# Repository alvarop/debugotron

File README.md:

# Debugotron!

Debugotron is a collection of debugging/automation tools I've wanted in the past but didn't have access to. Currently, the tools include:

## SWD to USB-C!

Have you ever wanted to debug your device over USB-C? Sometimes there's not enough room for a JTAG/SWD connector, or even TAGConnect pads! The USB-C specification has a Debug Accessory Mode feature that allows for this. I have a [Twitter thread](https://twitter.com/alvaroprieto/status/1495860045728395278) with additional details. [Here's an unrolled version for easier reading.](https://threadreaderapp.com/thread/1495860045728395278.html)

### SWD to USB-C Programmer
Since the current adapter uses an ATTiny24a, I made a different programmer adapter for it

### Example Target
This is a simple STM32L4 board that implements USB-C DAM (the "proper way") as an example.

## SWD Switch
Tool that allows connecting/disconnecting the SWD/JTAG lines (Via ARM 10-pin connector) with a pushbutton (or external signal). This can be useful when trying to measure ultra low power consumption on a device while the debugger is connected (but not necessarily running/attached).

## USB-C Switch
This one is more of an automation tool. I've always wanted to automate firmware testing. Sometimes, having USB connected is necessary to program/communicate with a device, but at the same time, having USB connected changes the power characteristics of the test (or just operating mode).

For example, you might want to automatically test the power consumption of a battery powered device every night with the latest firmware. In order to run the test, you might have to connect to the device, flash it, then disconnect USB. The USB-C switch will allow software-controlled power and data connect/disconnects to a USB-C device. Depending on the configuration, it will also allow full 20V@5A pass-through by allowing USB-PD communication over the CC lines.

In the cases where you want to communicate with a device over USB while still powering it via 20V (or anything higher than 5V), a USB switch allows for a different USB cable to be used for data only, while power is taken from a separate USB-C port.

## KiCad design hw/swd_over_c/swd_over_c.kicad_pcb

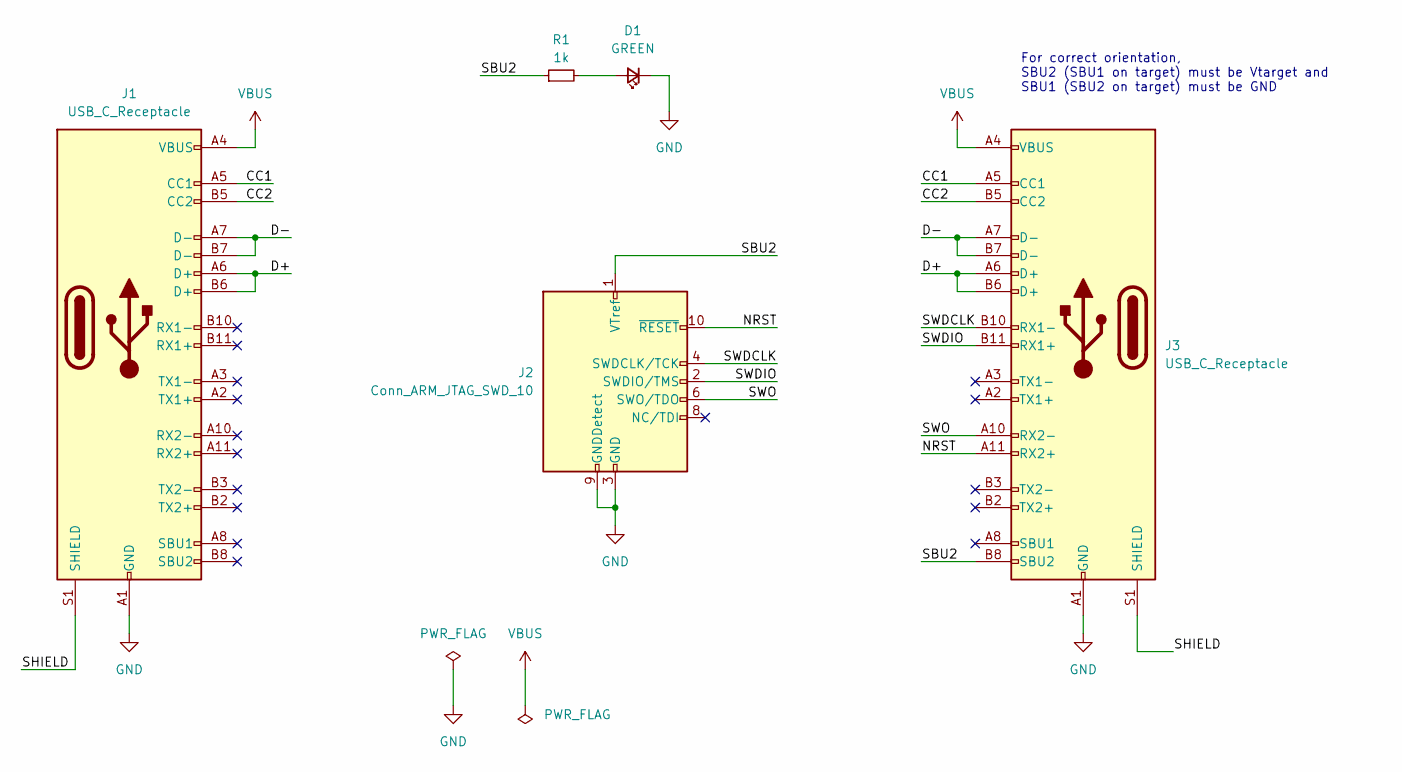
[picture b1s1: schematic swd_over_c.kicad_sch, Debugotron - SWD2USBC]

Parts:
D1: GREEN; LED_0603_1608Metric; MPN SML-D12M8WT86
J1, J3: USB_C_Receptacle; MOLEX-1054500101
J2: Conn_ARM_JTAG_SWD_10; SAMTEC_FTSH-105-01-F-DV-P-TR; MPN FTSH-105-01-F-DV-K
R1: 1k; R_0402_1005Metric; MPN RC0402FR-071KL

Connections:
/CC1: J1.A5 (CC1), J3.A5 (CC1)
/CC2: J1.B5 (CC2), J3.B5 (CC2)
/D+: J1.A6 (D+), J1.B6 (D+), J3.A6 (D+), J3.B6 (D+)
/D-: J1.A7 (D-), J1.B7 (D-), J3.A7 (D-), J3.B7 (D-)
/NRST: J2.10 (~RESET), J3.A11 (RX2+)
/SBU2: J2.1 (VTref), J3.B8 (SBU2), R1.1
/SHIELD: J1.S1 (SHIELD), J3.S1 (SHIELD)
/SWDCLK: J2.4 (SWDCLK/TCK), J3.B10 (RX1-)
/SWDIO: J2.2 (SWDIO/TMS), J3.B11 (RX1+)
/SWO: J2.6 (SWO/TDO), J3.A10 (RX2-)
GND: D1.1 (K), J1.A1 (GND), J1.A12 (GND), J1.B1 (GND), J1.B12 (GND), J2.3 (GND), J2.5 (GND), J2.9 (GNDDetect), J3.A1 (GND), J3.A12 (GND), J3.B1 (GND), J3.B12 (GND)
unnamed: D1.2 (A), R1.2
VBUS: J1.A4 (VBUS), J1.A9 (VBUS), J1.B4 (VBUS), J1.B9 (VBUS), J3.A4 (VBUS), J3.A9 (VBUS), J3.B4 (VBUS), J3.B9 (VBUS)

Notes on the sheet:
For correct orientation, SBU2 (SBU1 on target) must be Vtarget and SBU1 (SBU2 on target) must be GND

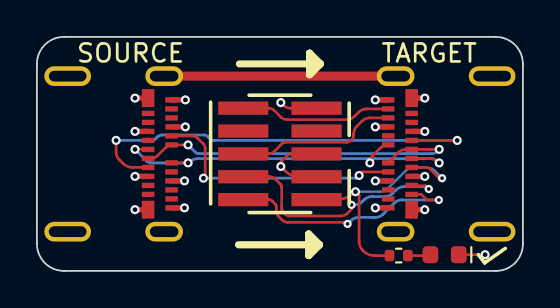
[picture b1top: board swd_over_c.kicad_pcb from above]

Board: 4 copper layers, 27.0 x 13.0 mm, 5 parts (0 on the bottom side), 13 nets.

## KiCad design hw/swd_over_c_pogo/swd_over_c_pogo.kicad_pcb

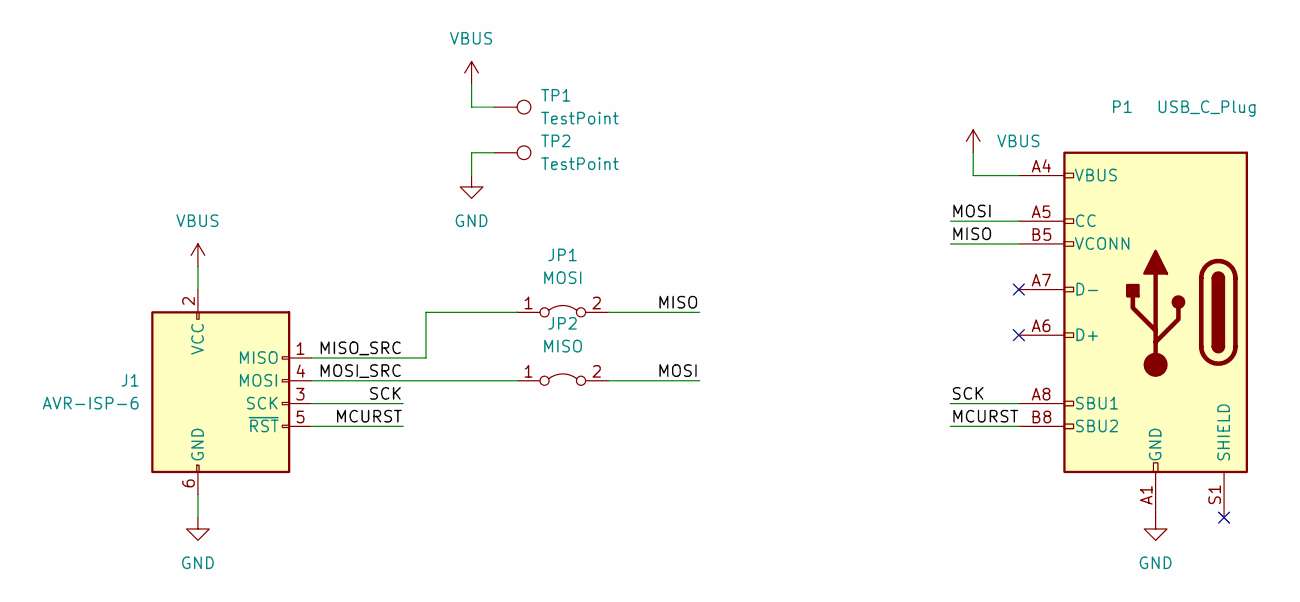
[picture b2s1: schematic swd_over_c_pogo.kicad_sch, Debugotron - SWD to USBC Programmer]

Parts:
J1: AVR-ISP-6; IDC-Header_2x03_P2.54mm_Vertical; MPN 30306-6002HB
JP1: MOSI; SolderJumper-2_P1.3mm_Bridged_RoundedPad1.0x1.5mm
JP2: MISO; SolderJumper-2_P1.3mm_Bridged_RoundedPad1.0x1.5mm
P1: USB_C_Plug; TYPE-C-31-G-06; MPN TYPE-C-31-G-06
TP1, TP2: TestPoint; TestPoint_Pad_D2.5mm

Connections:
/MCURST: J1.5 (~RST), P1.B8 (SBU2)
/MISO: JP1.2 (B), P1.B5 (VCONN)
/MISO_SRC: J1.1 (MISO), JP1.1 (A)
/MOSI: JP2.2 (B), P1.A5 (CC)
/MOSI_SRC: J1.4 (MOSI), JP2.1 (A)
/SCK: J1.3 (SCK), P1.A8 (SBU1)
GND: J1.6 (GND), P1.A1 (GND), P1.A12 (GND), P1.B1 (GND), P1.B12 (GND), TP2.1
VBUS: J1.2 (VCC), P1.A4 (VBUS), P1.A9 (VBUS), P1.B4 (VBUS), P1.B9 (VBUS), TP1.1

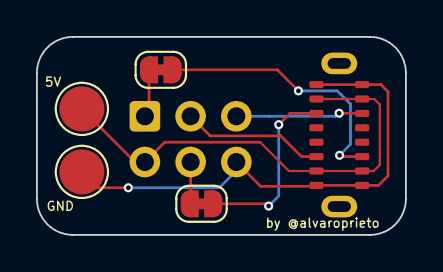
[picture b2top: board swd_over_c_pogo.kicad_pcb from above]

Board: 2 copper layers, 20.5 x 11.0 mm, 6 parts (1 on the bottom side), 8 nets.

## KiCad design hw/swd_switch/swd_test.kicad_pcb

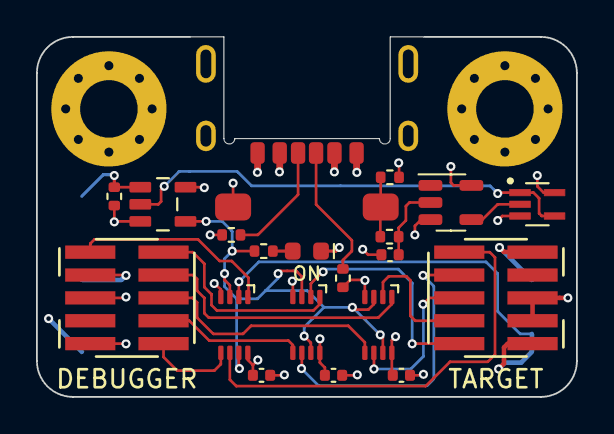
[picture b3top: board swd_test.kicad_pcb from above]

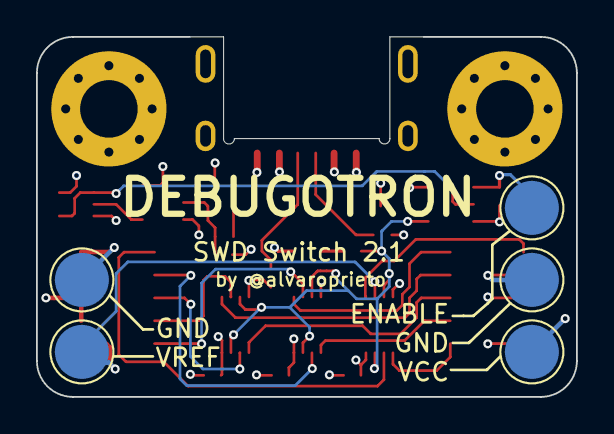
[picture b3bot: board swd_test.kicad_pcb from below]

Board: 4 copper layers, 30.0 x 20.0 mm, 26 parts (5 on the bottom side), 23 nets.

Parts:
C1, C2, C3, C4: 0.1uF; C_0402_1005Metric
D1: LED; LED_0603_1608Metric
J2: USB_C_Receptacle_USB2.0; USB4515-GF-A
J3: SWD_IN; SAMTEC_FTSH-105-01-F-DV-P-TR_alt
J5: SWD_OUT; SAMTEC_FTSH-105-01-F-DV-P-TR_alt
R1, R2, R3, R4, R5, R6: 5.1k; R_0402_1005Metric
SW1: SW_Push; PTS636_G
TP1, TP2, TP3, TP4, TP5: TestPoint; TestPoint_Pad_D3.0mm
U1: SN74LVC1G80DCKR; SOT65P210X110-5N
U2: SN74LVC1G32DBVR; SOT95P280X145-5N
U3, U4, U5: SN74LVC2G66; SN74LVC2G66-VSSOP
U6: SN74AHC1G14; SOT-23-5

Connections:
/RESET: J3.10 (~RESET), U4.5 (2A)
/RESET_OUT: J5.10 (~RESET), U4.6 (2B)
/SWDCLK_TCK: J3.4 (SWDCLK/TCK), U3.1 (1A)
/SWDCLK_TCK_OUT: J5.4 (SWDCLK/TCK), U3.2 (1B)
/SWDIO_TMS: J3.2 (SWDIO/TMS), U5.1 (1A)
/SWDIO_TMS_OUT: J5.2 (SWDIO/TMS), U5.2 (1B)
/SWD_EN: R6.1, U2.4, U3.3 (2C), U3.7 (1C), U4.3 (2C), U4.7 (1C), U5.3 (2C), U5.7 (1C)
/SWD_EN_BTN: U1.1 (D), U1.4 (~Q), U2.2
/SWD_EN_EXT: R3.1, TP3.1, U2.1
/SWO_TDO: J3.6 (SWO/TDO), U3.5 (2A)
/SWO_TDO_OUT: J5.6 (SWO/TDO), U3.6 (2B)
/TDI: J3.8 (NC/TDI), U5.5 (2A)
/TDI_OUT: J5.8 (NC/TDI), U5.6 (2B)
/VREF: J3.1 (VTref), U4.1 (1A)
/VREF_OUT: J5.1 (VTref), TP5.1, U4.2 (1B)
GND: C1.2, C2.2, C3.2, C4.2, D1.1 (K), J2.A12 (GND), J2.B12 (GND), J3.3 (GND), J3.5 (GND), J3.9 (GNDDetect), J5.3 (GND), J5.5 (GND), J5.9 (GNDDetect), R3.2, R4.2, R5.2, SW1.1, TP2.1, TP4.1, U1.3 (GND), U2.3 (GND), U3.4 (GND), U4.4 (GND), U5.4 (GND), U6.3 (GND)
unnamed: D1.2 (A), R6.2
unnamed: J2.A5 (CC1), R5.1
unnamed: J2.B5 (CC2), R4.1
unnamed: R1.2, R2.1, SW1.2
unnamed: C1.1, R2.2, U6.2
unnamed: U1.2 (CLK), U6.4
VCC: C2.1, C3.1, C4.1, J2.A9 (VBUS), J2.B9 (VBUS), R1.1, TP1.1, U1.5 (VCC), U2.5 (VCC), U3.8 (VCC), U4.8 (VCC), U5.8 (VCC), U6.5 (VCC)

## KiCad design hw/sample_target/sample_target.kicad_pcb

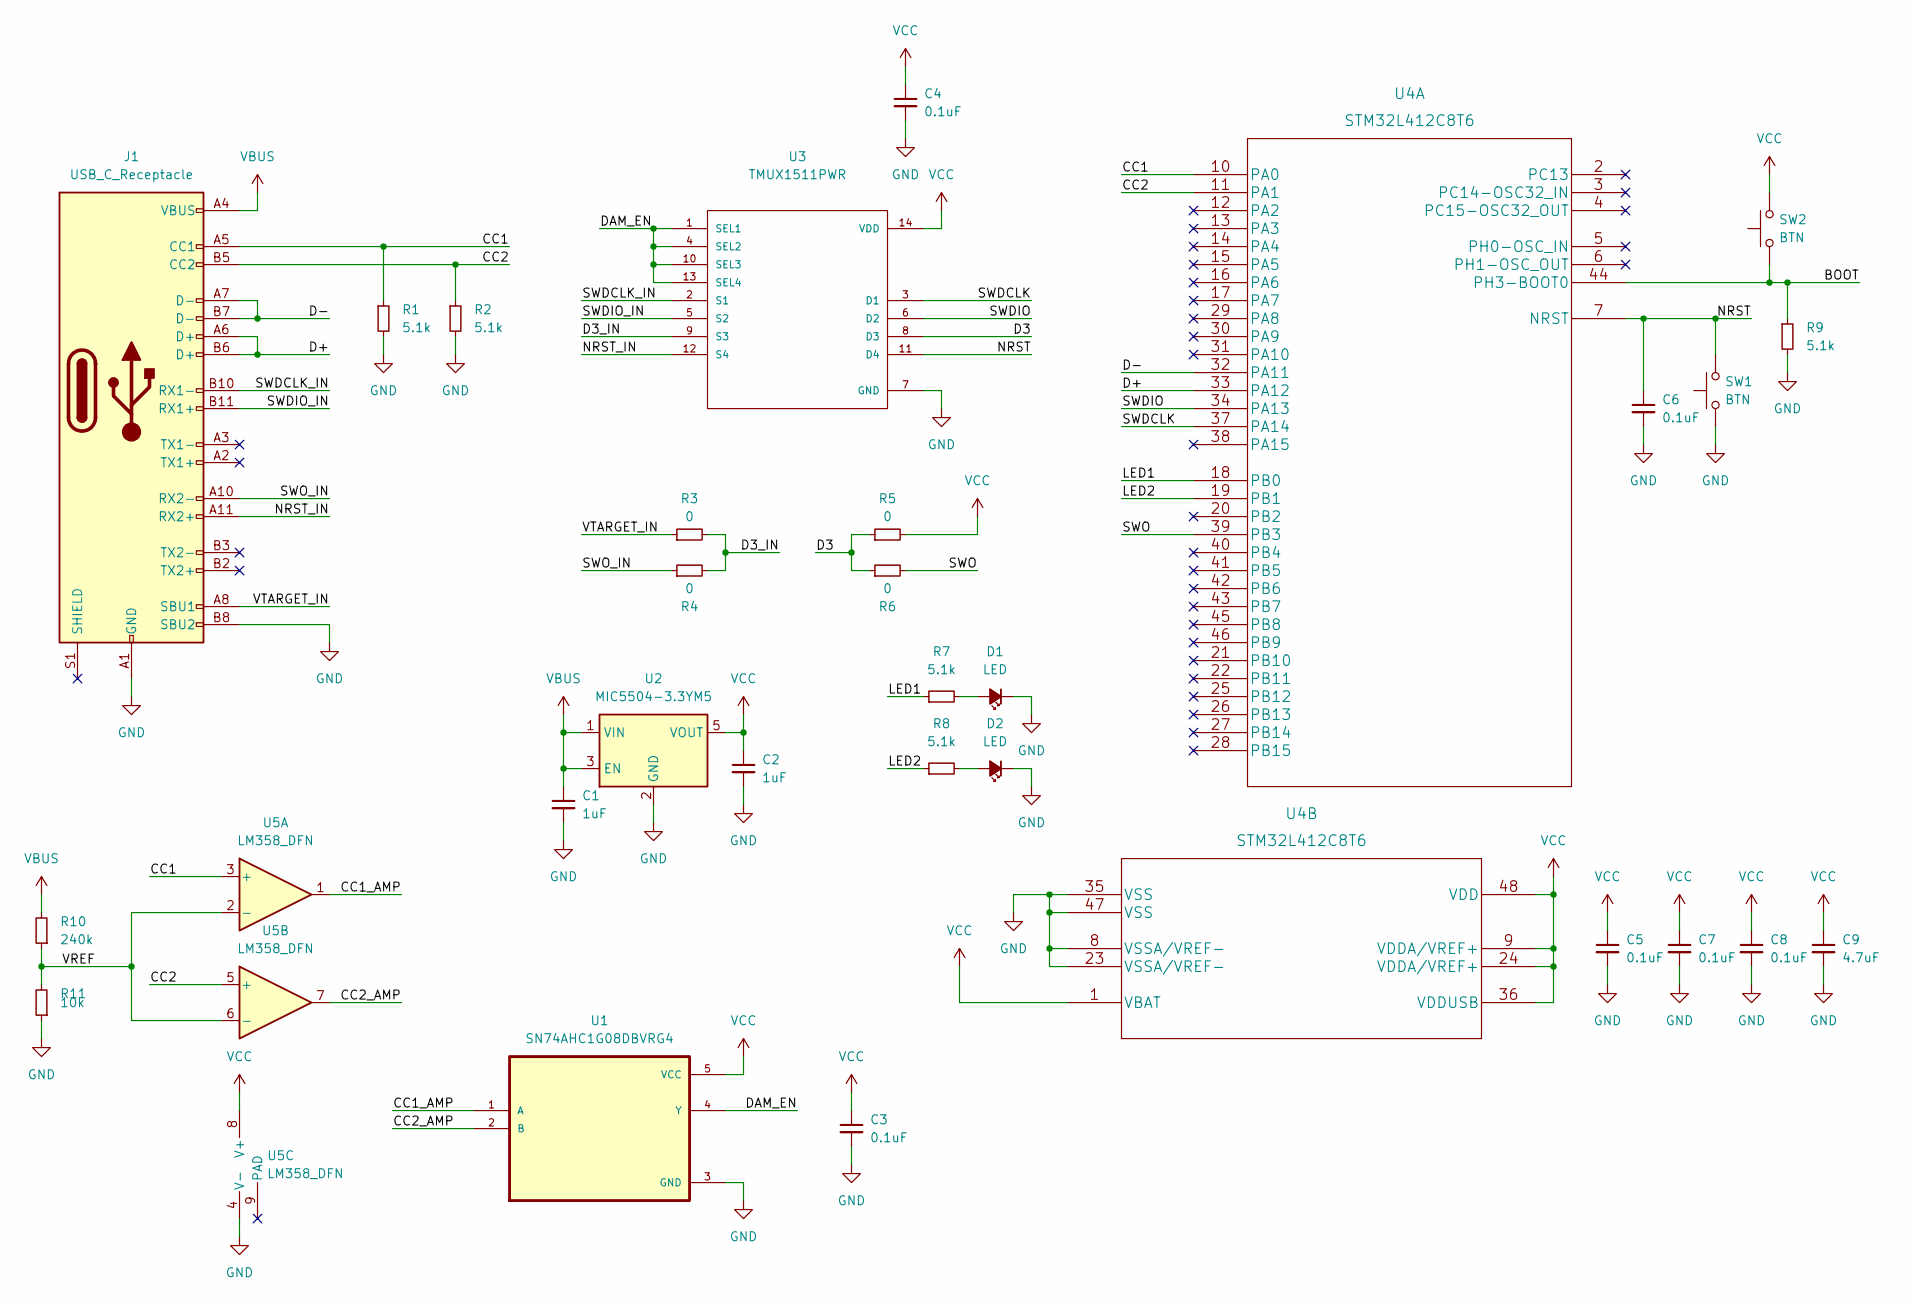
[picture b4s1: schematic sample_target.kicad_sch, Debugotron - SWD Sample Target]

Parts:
C1, C2: 1uF; C_0402_1005Metric
C3, C4, C5, C6, C7, C8: 0.1uF; C_0402_1005Metric
C9: 4.7uF; C_0402_1005Metric
D1, D2: LED; LED_0603_1608Metric
J1: USB_C_Receptacle; GCT_USB4056-03-A_REVA_MOD
R1, R2, R7, R8, R9: 5.1k; R_0402_1005Metric
R3, R4, R5, R6: 0; R_0402_1005Metric
R10: 240k; R_0402_1005Metric
R11: 10k; R_0402_1005Metric
SW1, SW2: BTN; PTS820J25MSMTRLFS
U1: SN74AHC1G08DBVRG4; SOT95P280X145-5N
U2: MIC5504-3.3YM5; SOT-23-5
U3: TMUX1511PWR; SOP65P640X120-14N
U4: STM32L412C8T6
U5: LM358_DFN; DFN-8-1EP_2x2mm_P0.5mm_EP1.05x1.75mm

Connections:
/BOOT: R9.1, SW2.1, U4.44 (PH3-BOOT0)
/CC1: J1.A5 (CC1), R1.1, U4.10 (PA0), U5.3 (+)
/CC1_AMP: U1.1 (A), U5.1
/CC2: J1.B5 (CC2), R2.1, U4.11 (PA1), U5.5 (+)
/CC2_AMP: U1.2 (B), U5.7
/D3: R5.1, R6.1, U3.8 (D3)
/D3_IN: R3.2, R4.2, U3.9 (S3)
/D+: J1.A6 (D+), J1.B6 (D+), U4.33 (PA12)
/D-: J1.A7 (D-), J1.B7 (D-), U4.32 (PA11)
/DAM_EN: U1.4 (Y), U3.1 (SEL1), U3.4 (SEL2), U3.10 (SEL3), U3.13 (SEL4)
/LED1: R7.1, U4.18 (PB0)
/LED2: R8.1, U4.19 (PB1)
/NRST: C6.1, SW1.2, U3.11 (D4), U4.7 (NRST)
/NRST_IN: J1.A11 (RX2+), U3.12 (S4)
/SWDCLK: U3.3 (D1), U4.37 (PA14)
/SWDCLK_IN: J1.B10 (RX1-), U3.2 (S1)
/SWDIO: U3.6 (D2), U4.34 (PA13)
/SWDIO_IN: J1.B11 (RX1+), U3.5 (S2)
/SWO: R6.2, U4.39 (PB3)
/SWO_IN: J1.A10 (RX2-), R4.1
/VREF: R10.1, R11.2, U5.2 (-), U5.6 (-)
/VTARGET_IN: J1.A8 (SBU1), R3.1
GND: C1.2, C2.2, C3.2, C4.2, C5.2, C6.2, C7.2, C8.2, C9.2, D1.1 (K), D2.1 (K), J1.A1 (GND), J1.A12 (GND), J1.B1 (GND), J1.B8 (SBU2), J1.B12 (GND), R1.2, R2.2, R9.2, R11.1, SW1.1, U1.3 (GND), U2.2 (GND), U3.7 (GND), U4.8 (VSSA/VREF-), U4.23 (VSSA/VREF-), U4.35 (VSS), U4.47 (VSS), U5.4 (V-)
unnamed: D1.2 (A), R7.2
unnamed: D2.2 (A), R8.2
VBUS: C1.1, J1.A4 (VBUS), J1.A9 (VBUS), J1.B4 (VBUS), J1.B9 (VBUS), R10.2, U2.1 (VIN), U2.3 (EN)
VCC: C2.1, C3.1, C4.1, C5.1, C7.1, C8.1, C9.1, R5.2, SW2.2, U1.5 (VCC), U2.5 (VOUT), U3.14 (VDD), U4.1 (VBAT), U4.9 (VDDA/VREF+), U4.24 (VDDA/VREF+), U4.36 (VDDUSB), U4.48 (VDD), U5.8 (V+)

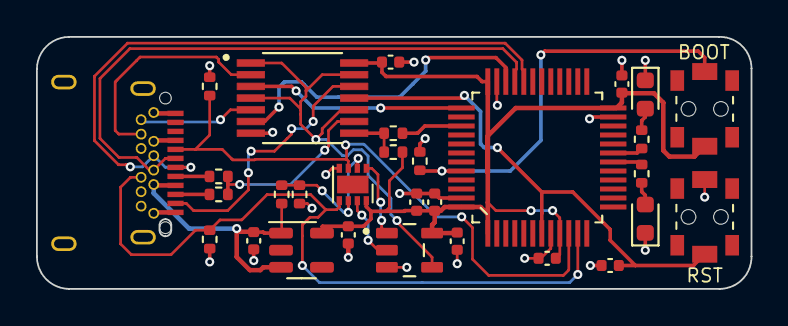
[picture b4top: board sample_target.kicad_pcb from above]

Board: 2 copper layers, 39.7 x 14.0 mm, 30 parts (0 on the bottom side), 27 nets.

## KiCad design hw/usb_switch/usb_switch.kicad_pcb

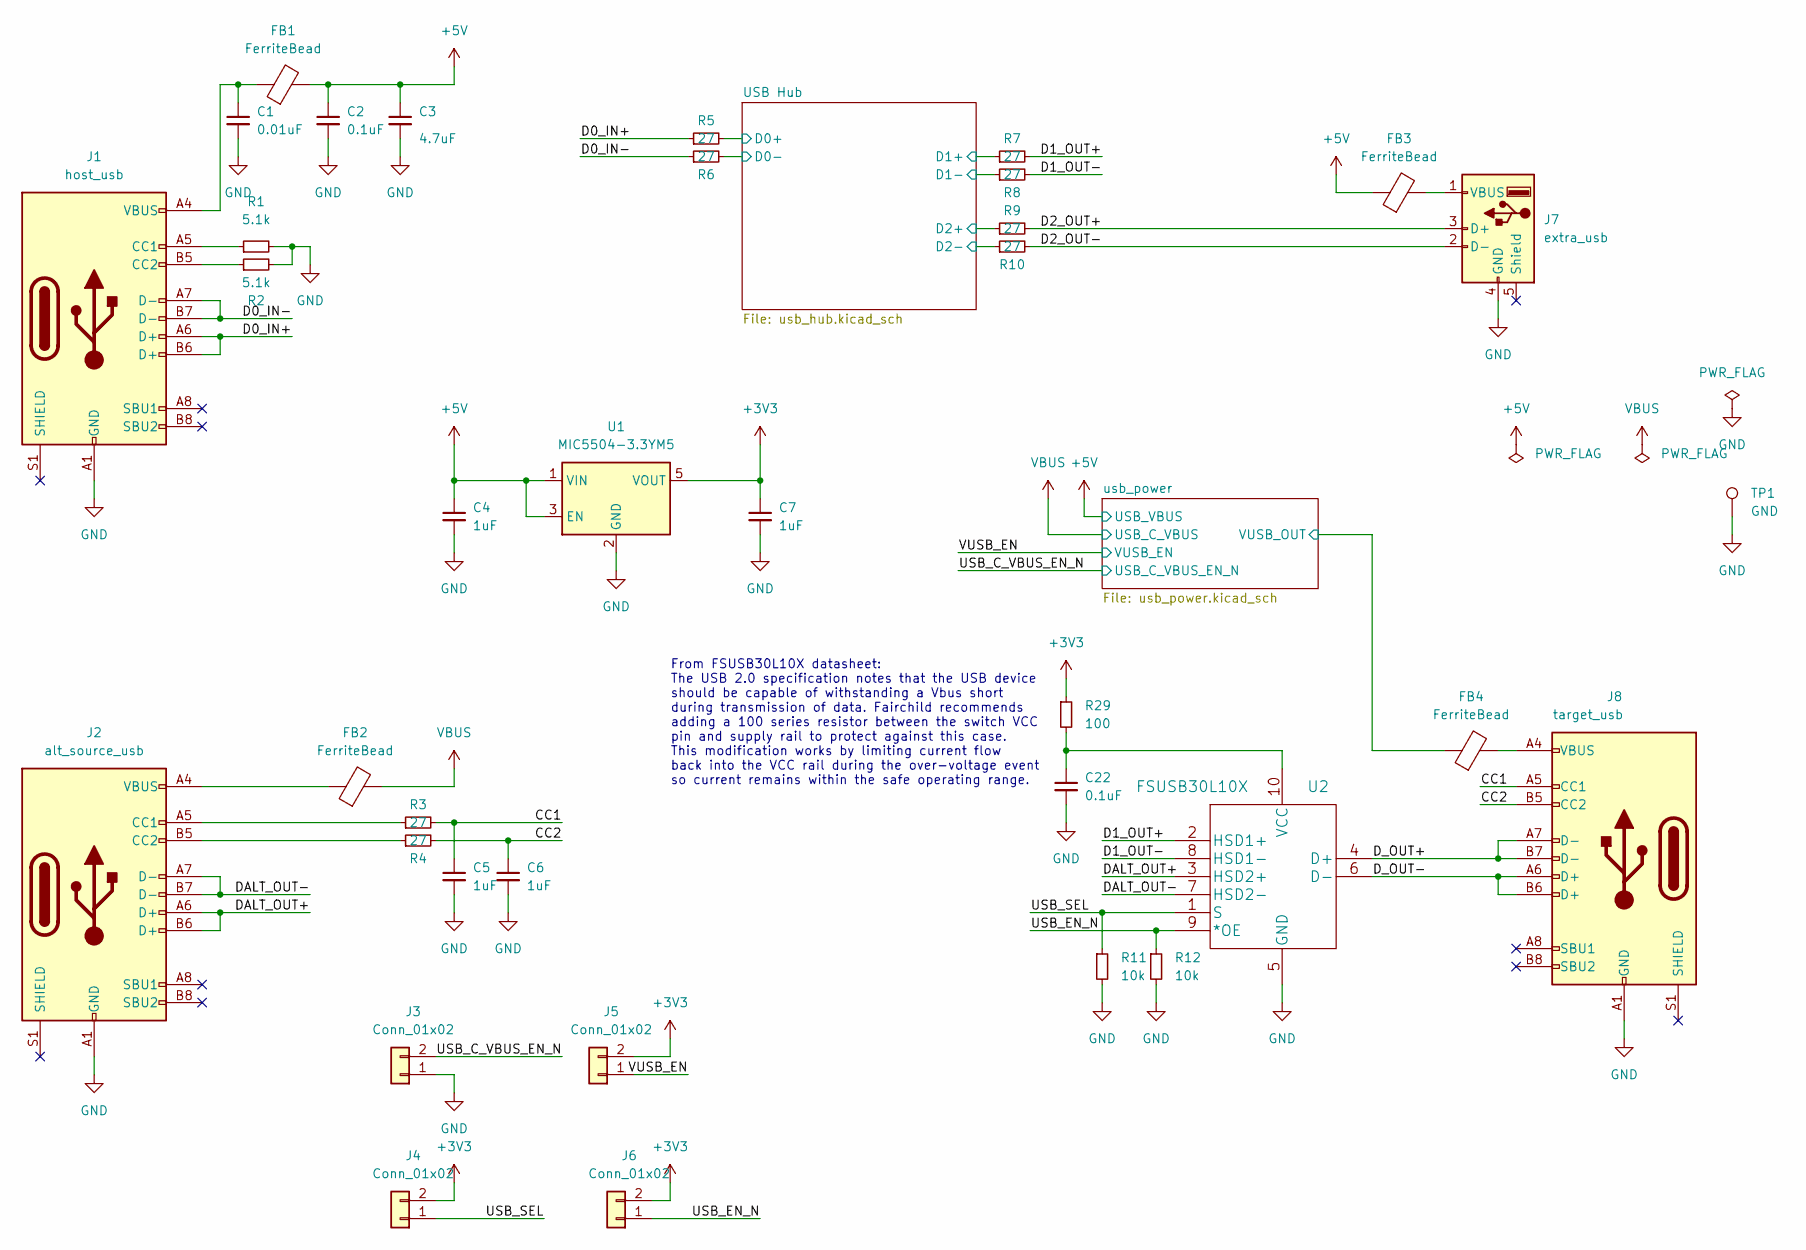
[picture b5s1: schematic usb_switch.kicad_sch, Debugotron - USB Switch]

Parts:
C1: 0.01uF; C_0402_1005Metric
C2, C22: 0.1uF; C_0402_1005Metric
C3: 4.7uF; C_0805_2012Metric
C4, C5, C6, C7: 1uF; C_0402_1005Metric
FB1, FB2, FB3, FB4: FerriteBead; L_0603_1608Metric
J1: host_usb; USB4105-GF-A
J2: alt_source_usb; USB4105-GF-A
J3, J4, J5, J6: Conn_01x02; PinSocket_1x02_P2.54mm_Vertical
J7: extra_usb; UE27ACX410X
J8: target_usb; USB4105-GF-A
R1, R2: 5.1k; R_0402_1005Metric
R3, R4, R5, R6, R7, R8, R9, R10: 27; R_0402_1005Metric
R11, R12: 10k; R_0402_1005Metric
R29: 100; R_0402_1005Metric
TP1: GND; RCWCTE
U1: MIC5504-3.3YM5; SOT-23-5
U2: FSUSB30L10X; MSOP-10_3x3mm_P0.5mm

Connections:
+3V3: C7.1, J4.2, J5.2, J6.2, R29.1, U1.5 (VOUT); also elsewhere on the board
+5V: C2.1, C3.1, C4.1, FB1.2, FB3.1, U1.1 (VIN), U1.3 (EN); also elsewhere on the board
/CC1: C5.1, J8.A5 (CC1), R3.2
/CC2: C6.1, J8.B5 (CC2), R4.2
/D0_IN+: J1.A6 (D+), J1.B6 (D+), R5.1
/D0_IN-: J1.A7 (D-), J1.B7 (D-), R6.1
/D1_OUT+: R7.2, U2.2 (HSD1+)
/D1_OUT-: R8.2, U2.8 (HSD1-)
/D2_OUT+: J7.3 (D+), R9.2
/D2_OUT-: J7.2 (D-), R10.2
/DALT_OUT+: J2.A6 (D+), J2.B6 (D+), U2.3 (HSD2+)
/DALT_OUT-: J2.A7 (D-), J2.B7 (D-), U2.7 (HSD2-)
/D_OUT+: J8.A7 (D-), J8.B7 (D-), U2.4 (D+)
/D_OUT-: J8.A6 (D+), J8.B6 (D+), U2.6 (D-)
/USB Hub/D0+: R5.2; also elsewhere on the board
/USB Hub/D0-: R6.2; also elsewhere on the board
/USB Hub/D1+: R7.1; also elsewhere on the board
/USB Hub/D1-: R8.1; also elsewhere on the board
/USB Hub/D2+: R9.1; also elsewhere on the board
/USB Hub/D2-: R10.1; also elsewhere on the board
/USB_C_VBUS_EN_N: J3.2; also elsewhere on the board
/USB_EN_N: J6.1, R12.1, U2.9 (*OE)
/USB_SEL: J4.1, R11.1, U2.1 (S)
/VUSB_EN: J5.1; also elsewhere on the board
/usb_power/VUSB_OUT: FB4.1; also elsewhere on the board
GND: C1.2, C2.2, C3.2, C4.2, C5.2, C6.2, C7.2, C22.2, J1.A1 (GND), J1.A12 (GND), J1.B1 (GND), J1.B12 (GND), J2.A1 (GND), J2.A12 (GND), J2.B1 (GND), J2.B12 (GND), J3.1, J7.4 (GND), J8.A1 (GND), J8.A12 (GND), J8.B1 (GND), J8.B12 (GND), R1.2, R2.2, R11.2, R12.2, TP1.1, U1.2 (GND), U2.5 (GND); also elsewhere on the board
unnamed: C1.1, FB1.1, J1.A4 (VBUS), J1.A9 (VBUS), J1.B4 (VBUS), J1.B9 (VBUS)
unnamed: FB2.1, J2.A4 (VBUS), J2.A9 (VBUS), J2.B4 (VBUS), J2.B9 (VBUS)
unnamed: FB3.2, J7.1 (VBUS)
unnamed: FB4.2, J8.A4 (VBUS), J8.A9 (VBUS), J8.B4 (VBUS), J8.B9 (VBUS)
unnamed: J1.A5 (CC1), R1.1
unnamed: J1.B5 (CC2), R2.1
unnamed: J2.A5 (CC1), R3.1
unnamed: J2.B5 (CC2), R4.1
unnamed: C22.1, R29.2, U2.10 (VCC)
VBUS: FB2.2; also elsewhere on the board

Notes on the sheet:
From FSUSB30L10X datasheet: The USB 2.0 specification notes that the USB device should be capable of withstanding a Vbus short during transmission of data. Fairchild recommends adding a 100 series resistor between the switch VCC pin and supply rail to protect against this case. This modification wo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

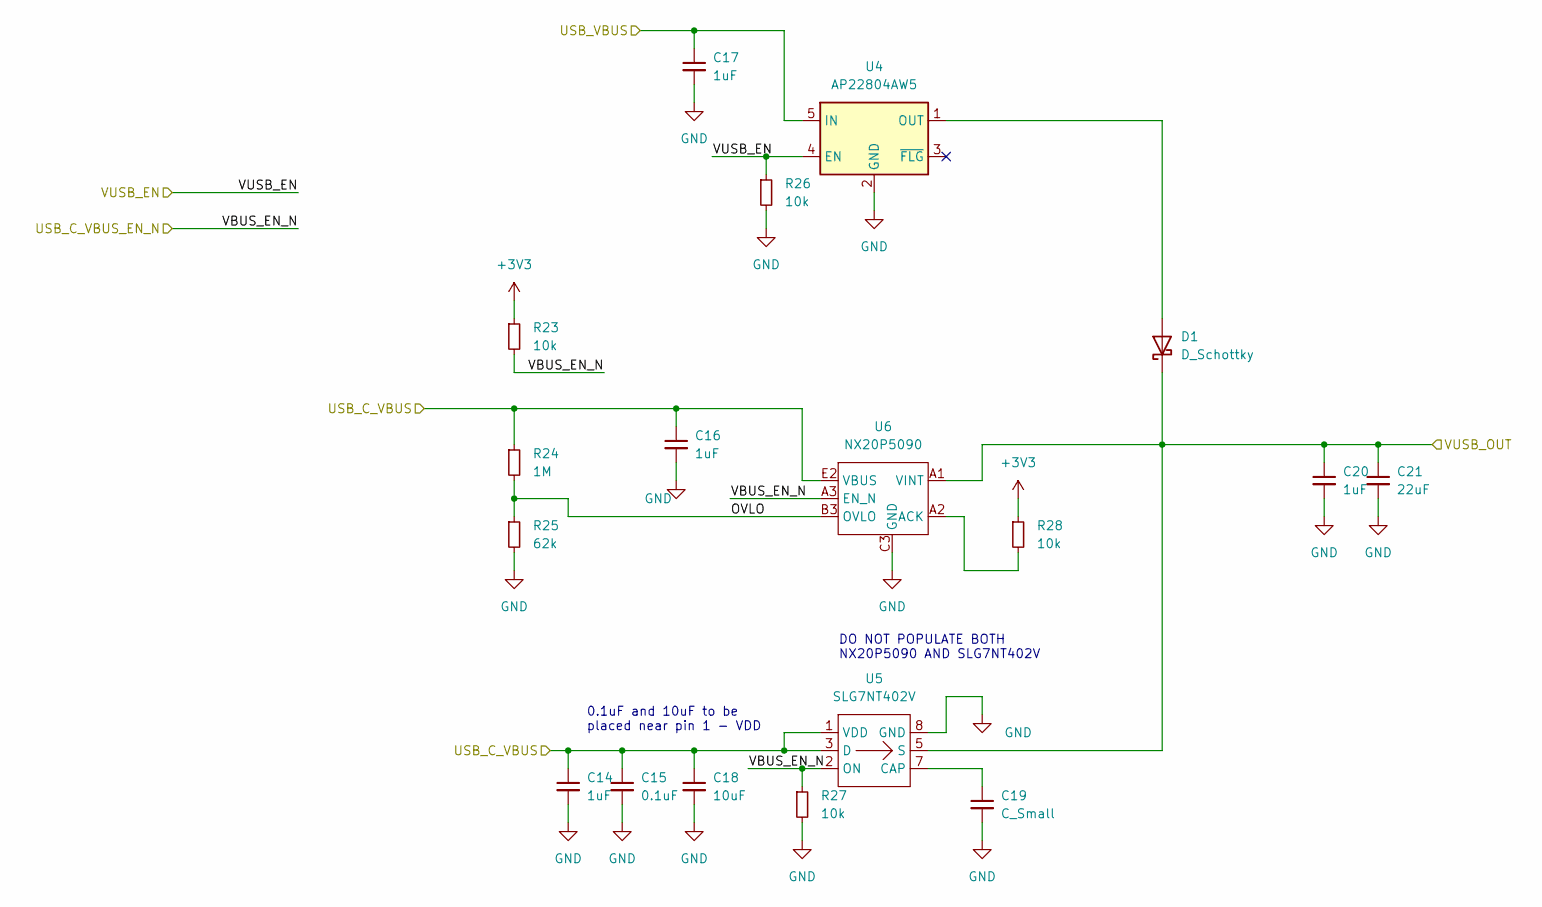
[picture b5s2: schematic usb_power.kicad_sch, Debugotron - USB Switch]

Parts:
C14, C16, C17, C20: 1uF; C_0402_1005Metric
C15: 0.1uF; C_0402_1005Metric
C18: 10uF; C_0603_1608Metric
C19: C_Small; C_0402_1005Metric
C21: 22uF; C_0805_2012Metric
D1: D_Schottky; CD123-B140LR
R23, R26, R27, R28: 10k; R_0402_1005Metric
R24: 1M; R_0402_1005Metric
R25: 62k; R_0402_1005Metric
U4: AP22804AW5; SOT-23-5
U5: SLG7NT402V; FC-TDFN-8
U6: NX20P5090; NX20P5090UK

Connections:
+3V3: R23.1, R28.1; also elsewhere on the board
+5V: C17.1, U4.5 (IN); also elsewhere on the board
/USB_C_VBUS_EN_N: R23.2, R27.1, U5.2 (ON), U6.A3 (EN_N); also elsewhere on the board
/VUSB_EN: R26.1, U4.4 (EN); also elsewhere on the board
/usb_power/OVLO: R24.2, R25.1, U6.B3 (OVLO)
/usb_power/VUSB_OUT: C20.1, C21.1, D1.1 (K), U5.5 (S), U6.A1 (VINT), U6.B1 (VINT), U6.C1 (VINT), U6.D1 (VINT); also elsewhere on the board
GND: C14.2, C15.2, C16.2, C17.2, C18.2, C19.2, C20.2, C21.2, R25.2, R26.2, R27.2, U4.2 (GND), U5.8 (GND), U6.C3 (GND), U6.D3 (GND), U6.E3 (GND); also elsewhere on the board
unnamed: C19.1, U5.7 (CAP)
unnamed: D1.2 (A), U4.1 (OUT)
unnamed: R28.2, U6.A2 (ACK)
VBUS: C14.1, C15.1, C16.1, C18.1, R24.1, U5.1 (VDD), U5.3 (D), U6.B2 (VBUS), U6.C2 (VBUS), U6.D2 (VBUS), U6.E1 (VBUS), U6.E2 (VBUS); also elsewhere on the board

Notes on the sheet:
DO NOT POPULATE BOTH NX20P5090 AND SLG7NT402V
0.1uF and 10uF to be placed near pin 1 - VDD

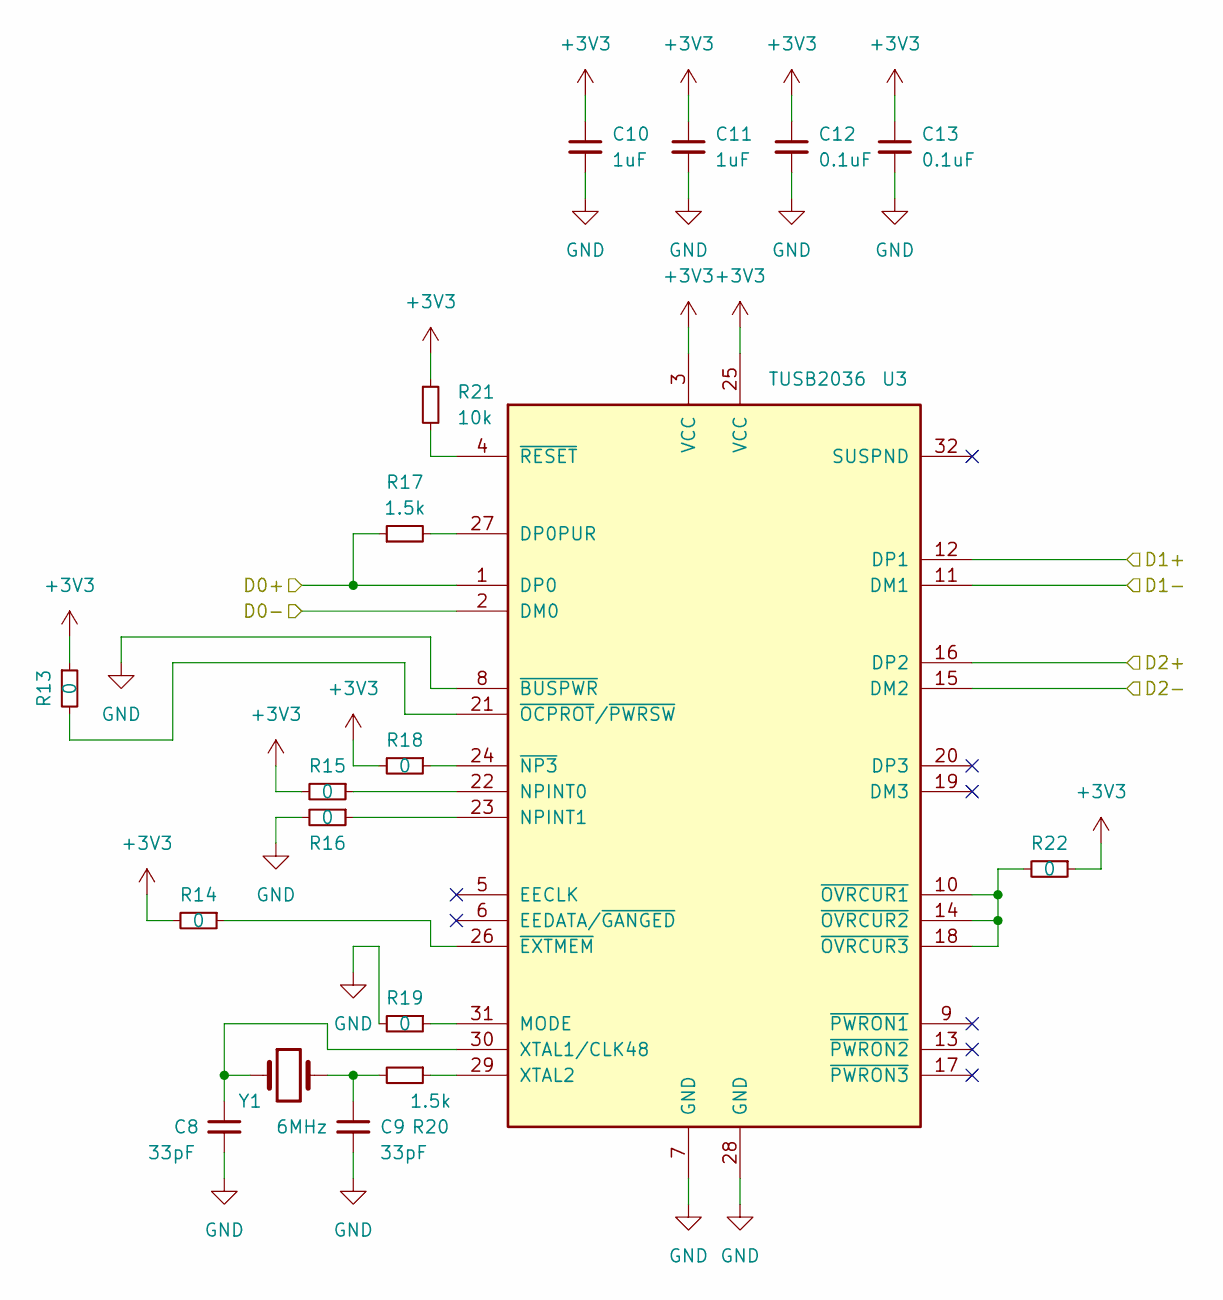
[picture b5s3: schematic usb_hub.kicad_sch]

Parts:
C8, C9: 33pF; C_0402_1005Metric
C10, C11: 1uF; C_0402_1005Metric
C12, C13: 0.1uF; C_0402_1005Metric
R13, R14, R15, R16, R18, R19, R22: 0; R_0402_1005Metric
R17, R20: 1.5k; R_0402_1005Metric
R21: 10k; R_0402_1005Metric
U3: TUSB2036; LQFP-32_7x7mm_P0.8mm
Y1: 6MHz; Crystal_SMD_HC49-SD

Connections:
+3V3: C10.1, C11.1, C12.1, C13.1, R13.1, R14.2, R15.2, R18.2, R21.1, R22.1, U3.3 (VCC), U3.25 (VCC); also elsewhere on the board
/USB Hub/D0+: R17.1, U3.1 (DP0); also elsewhere on the board
/USB Hub/D0-: U3.2 (DM0); also elsewhere on the board
/USB Hub/D1+: U3.12 (DP1); also elsewhere on the board
/USB Hub/D1-: U3.11 (DM1); also elsewhere on the board
/USB Hub/D2+: U3.16 (DP2); also elsewhere on the board
/USB Hub/D2-: U3.15 (DM2); also elsewhere on the board
GND: C8.2, C9.2, C10.2, C11.2, C12.2, C13.2, R16.2, R19.2, U3.7 (GND), U3.8 (~BUSPWR), U3.28 (GND); also elsewhere on the board
unnamed: C8.1, U3.30 (XTAL1/CLK48), Y1.1
unnamed: C9.1, R20.2, Y1.2
unnamed: R13.2, U3.21 (~OCPROT/~PWRSW)
unnamed: R14.1, U3.26 (~EXTMEM)
unnamed: R15.1, U3.22 (NPINT0)
unnamed: R16.1, U3.23 (NPINT1)
unnamed: R17.2, U3.27 (DP0PUR)
unnamed: R18.1, U3.24 (~NP3)
unnamed: R19.1, U3.31 (MODE)
unnamed: R20.1, U3.29 (XTAL2)
unnamed: R21.2, U3.4 (~RESET)
unnamed: R22.2, U3.10 (~OVRCUR1), U3.14 (~OVRCUR2), U3.18 (~OVRCUR3)

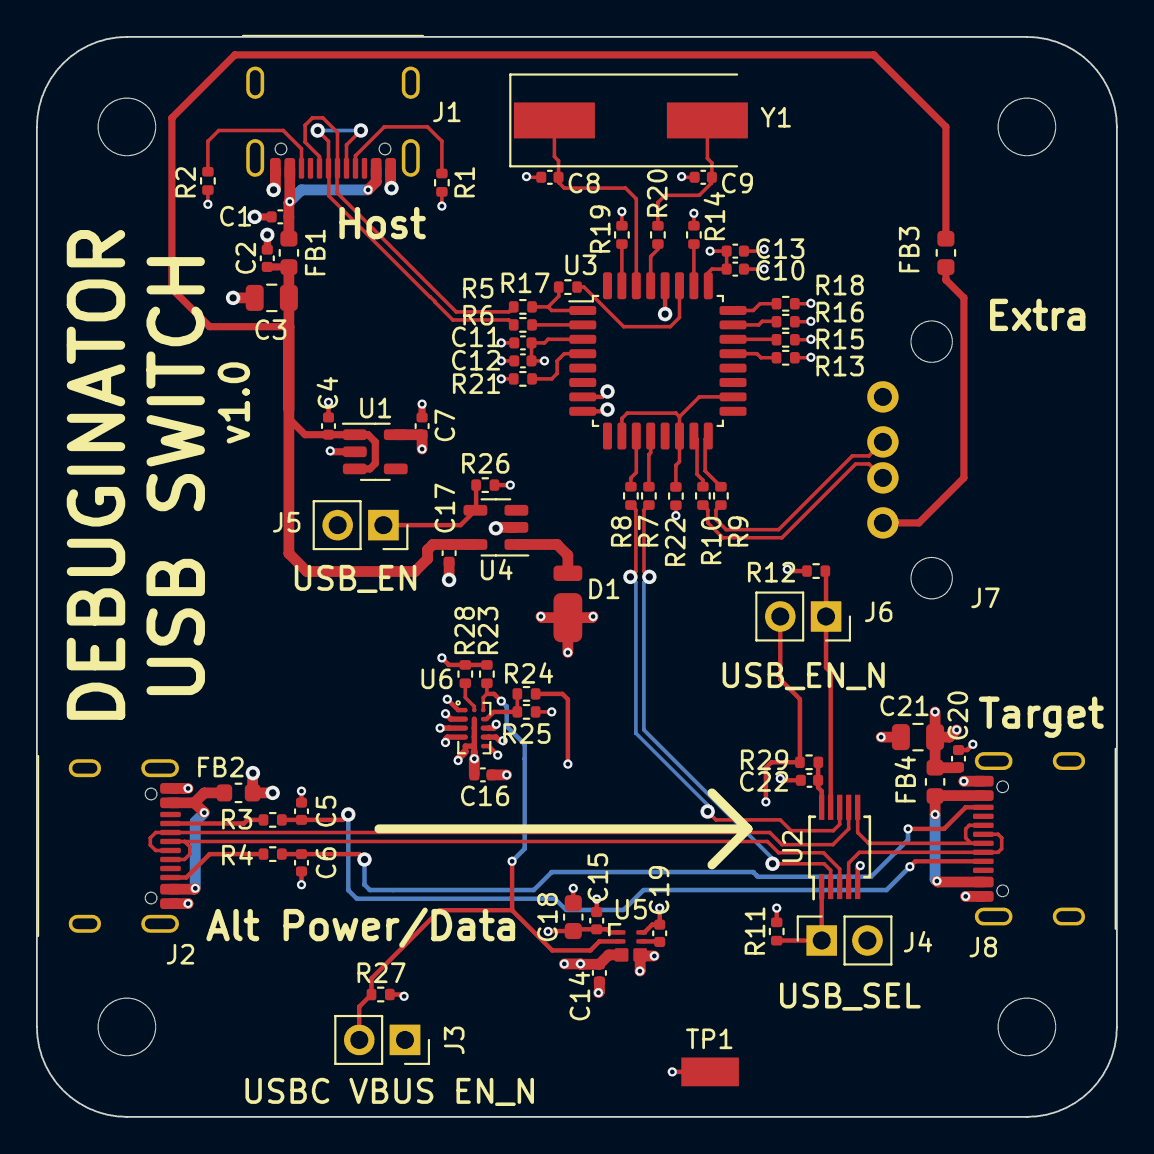
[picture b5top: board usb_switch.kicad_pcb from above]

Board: 4 copper layers, 60.0 x 60.0 mm, 72 parts (0 on the bottom side), 52 nets.

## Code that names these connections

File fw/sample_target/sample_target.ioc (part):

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Mcu.Name=STM32L412C8Tx
Mcu.Package=LQFP48
Mcu.UserName=STM32L412C8Tx
PA0.Signal=ADCx_IN5
PA1.Signal=ADCx_IN6
PA11.Mode=Device
PA11.Signal=USB_DM
PA12.Mode=Device
PA12.Signal=USB_DP
PB0.GPIOParameters=GPIO_Label
PB0.GPIO_Label=LED1
PB0.Signal=GPIO_Output
PB1.GPIOParameters=GPIO_Label
PB1.GPIO_Label=LED2
PB1.Signal=GPIO_Output
PH3-BOOT0\ (BOOT0).GPIOParameters=GPIO_Label
PH3-BOOT0\ (BOOT0).GPIO_Label=BOOT
PH3-BOOT0\ (BOOT0).Signal=GPIO_Input
RCC.HSE_VALUE=8000000
RCC.SYSCLKFreq_VALUE=80000000
RCC.SYSCLKSource=RCC_SYSCLKSOURCE_PLLCLK
board=custom

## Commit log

2021-11-14 Initial commit for debugotron SWD switch v1.0
2021-11-14 Start working on usb switch schematic
2021-11-15 Debugotron usb switch schematic almost done
    Ordered components
2021-11-16 Updating footprints
2021-12-03 Some part changes and started layout
2021-12-14 Finished and ordered from JLCPCB!
2022-01-16 Added MPNs and values to usb_switch
2022-01-16 Added MPNs for SWD_Switch
2022-01-16 Update gitignore
2022-01-16 Create LICENSE
2022-01-23 Adding swd over usb c v1.0 and pogo fixture
2022-01-24 Add sample target v1.0
2022-01-24 Add rpu calculator spreadsheet
2022-01-30 Add blink for ATTiny24 in swd-over-usb-c board
2022-02-07 Updated swd over c to v1.1 (and programmer)
2022-02-07 Switched to 0402 instead of 0201 components
2022-02-07 Added opamp to sample target
2022-02-14 Updated debugotron v2.0 and ordered
2022-02-20 Fully(?) working firmware to detect/set USB-C currents
2022-02-20 Rename firmware dir
2022-02-20 Minor bom updates
2022-02-20 Added sample target part numbers
2022-02-20 Starting sample target cubemx project
2022-02-20 Ignore html/pdf files
2022-02-20 Add cubemx project for sample target
2022-02-20 Let there be blinks!
2022-02-26 Updated SWD switch to 2.1
    Added schmitt trigger buffer to debounce circuit
2022-02-26 Rename swd_test -> swd_switch
2022-03-04 I forgot what I changed here
2022-03-04 SWD2USBC v1.2
2022-03-05 I should probably make a readme...
2022-03-05 Fixed MISO/MOSI swap and added BOM to swd2usbc
2022-03-05 Updating readme
2022-03-27 SWD over USB-C v1.4!!!
2022-03-27 Added alignment targets and drill filre origin
    Export for PCBWay
2022-05-15 v1.5
2022-05-20 v1.6 changes
2022-05-20 forgot the schematic changes
2022-06-08 Somehow got the values for R4 and R5 swapped...
    Swapped them in schematic and in code (manually reworked v1.6 boards to swap R4/R5)
2022-11-22 v2.0 SWD Over C
    Going to a different MCU since it's available at JLC and both USB-C connectors instead of plugs.
    _maybe_ this will work with a short USBC cable with all the conductors and make things much easier
2022-11-22 Make USB over C programmer v2.0 for JLC
    Hopefully it works
2022-11-23 Update footprint for USB plug
2022-12-03 Forgot to update the damn silkscreen...
2022-12-03 v3.0 SWD2USBC
    Had the tx/rx pairs flipped since I switched from USB-C Plug to Connector...
    Removed MCU since cables don't connect both CC1/CC2 so can't actually do a proper debug accessory mode.
    Should still work though?
2023-04-04 Release SWD over C v4.0
    Swapped Tx/Rx lines since USB C cables cross them over...
    Thanks to Matthias for reporting the bug!
2023-06-14 Minor changes for release package
2025-01-18 Fixed swd_over_c firmware
    One CC resistor was getting pulled up and the other down, which means
    that the CC1 and CC2 lines were not getting pulled up to 5V
    Now one gets pulled up and the other is set as an input to float
    How did this ever work>????

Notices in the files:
parts and their libraries:
Copyright 2021 Accelerated Designs. All rights reserved.
